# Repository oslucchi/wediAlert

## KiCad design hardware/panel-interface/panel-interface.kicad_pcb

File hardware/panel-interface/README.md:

# wediAlert fire panel interface

Replaces the hand-wired perfboard. Two supervised 12 V loops from the fire panel drive two relays,
whose contacts put 3.3 V on GPIO19 and GPIO26. It also carries the 12 V to 5 V module.
Open `panel-interface.kicad_pro` in KiCad 10.

| Condition | Loop | Relay | GPIO reads | wediAlert sees |
|---|---|---|---|---|
| Normal | closed | energized | 1 | normal |
| Alarm, panel power loss, cut cable | open | released | 0 | active |

No software change is needed: the pins and the logic match `GpioHandler`.

## Check before ordering

- **Board: 92 x 30 mm**, plus 7.5 mm of J1/J2 overhanging one long edge, for the box of 110 x 110 x 60 mm
  with the Pi and HAT alongside. Lay a paper cut-out in the box to check it clears the corner posts, and
  that the plugs and the panel cable have room to bend beyond the overhang.
- **Module: measured** at 52 x 23 mm with pads on a 50 x 21 mm rectangle (`MOD_*` in `gen_sch.py`). The
  board's 1.3 mm pad holes are an assumption: check them against the wire or pin you use.
- **Green plug: confirmed** 5.08 mm pitch.

## Parts

| Ref | Value | Notes |
|---|---|---|
| K1, K2 | FP2 D3009 | Reuse the existing relays. 5 V coil, 178 ohm, polarized |
| R1, R2 | 270 ohm, 0.6 W | Coil series resistor, about 0.2 W dissipated |
| D1, D2 | 1N4148 | Coil flyback. Band to the coil + side, as on the silk |
| F1, F2 | Bourns MF-R010 | Resettable, 100 mA hold, 5.08 mm pitch |
| D3, D4 | LED 3 mm, any color | Panel loop. 4 mA from 12 V |
| R3, R4 | 2.2 k | For D3, D4 |
| D5, D6 | LED 3 mm **red, orange or yellow** | Relay state. Blue or white will not light from 3.3 V |
| R5, R6 | 470 ohm | For D5, D6, about 3 mA |
| R7, R8 | 1 k | GPIO series protection |
| R9, R10 | 10 k | Pull-down. Overrides a leftover Pi pull-up |
| U1 | XL4015 module | Reuse the existing one |
| J1 | 4-way 5.08 mm MSTBA-style header | Mates with your existing green plug (5.08 mm confirmed) |
| J2 | 2-way 5.08 mm MSTBA-style header | 12 V in, with its plug |
| J3 | Solder pads | 5 V wires, 1 mm2 |
| J4 | 1x4 2.54 mm pin header | Dupont wires to the HAT |

The LED footprints can hold the LED directly, or take wires to LEDs on the box wall as today.

## Connections

| Connector | Pin | Signal | Goes to |
|---|---|---|---|
| J1 | 1 / 2 | Line 1 out / return | Panel fault loop |
| J1 | 3 / 4 | Line 2 out / return | Panel alarm loop |
| J2 | 1 / 2 | +12 V / GND | Supply, at least 2 A |
| J3 | 1 / 2 | +5 V / GND | HAT pin 2 / pin 6 |
| J4 | 1 | 3V3 | Pi pin 17 (**new wire**) |
| J4 | 2 | GPIO19 | Pi pin 35 |
| J4 | 3 | GPIO26 | Pi pin 37 |
| J4 | 4 | GND | Pi pin 39 |

Connector labels are on the bottom silkscreen, where they stay readable once parts are fitted.

| LED | Lit when |
|---|---|
| D3 / D5 | Line 1 loop closed / line 1 relay closed |
| D4 / D6 | Line 2 loop closed / line 2 relay closed |

The panel LED goes off for an alarm and for an unplugged cable alike, since both open the loop.

## Bring-up

Keep `wedialert` disabled until the last step.

1. **Before soldering each relay**, with a meter: 178 ohm or so between pins 1 and 10, and continuity
   between 8 and 9. Apply 5 V, + on pin 1 and - on pin 10: it should click, with continuity between
   8 and 7. The datasheet is a 2012 TE edition and these relays are older Alcatel parts, so this
   confirms the pinout before it matters.
2. **Module alone, Pi disconnected:** apply 12 V and set the trimmer to 5.1 V at J3.
3. **Connect J4 and J3 to the Pi.** Power up with nothing on J1. Both inputs must read 0, even after
   forcing a pull-up, because R9/R10 win:
   ```bash
   gpio -g mode 19 up; gpio -g mode 26 up; gpio -g read 19; gpio -g read 26
   ```
4. **Link J1 pins 1-2.** D3 and D5 light, the relay clicks, GPIO19 reads 1. Then the same with
   pins 3-4, for D4, D6 and GPIO26.
5. **Put back the pull-down**, as the service does, and measure 4.5 to 5 V across each coil:
   ```bash
   gpio -g mode 19 down; gpio -g mode 26 down
   ```
6. **On the panel**, check both inputs read 1, then enable the service. Warn the SMS contacts first.
   ```bash
   sudo systemctl enable --now wedialert
   ```

## Rebuilding

`generator/build.sh` regenerates everything from the scripts and runs ERC and DRC. It overwrites the
schematic and board, so hand edits made in KiCad are lost: once you start editing there, stop using it.

After moving a part on the board, run with `ROUTE_SEARCH=1` to find a new routing order (about 30 s per
attempt). The tracks were routed by a script: valid, but less tidy than hand routing.

`out/` holds the schematic PDF, BOM, Gerbers and drill files, and the ERC and DRC reports.

The DRC reports 2 accepted silkscreen warnings: the J1 and J2 outlines overhang the edge by design.

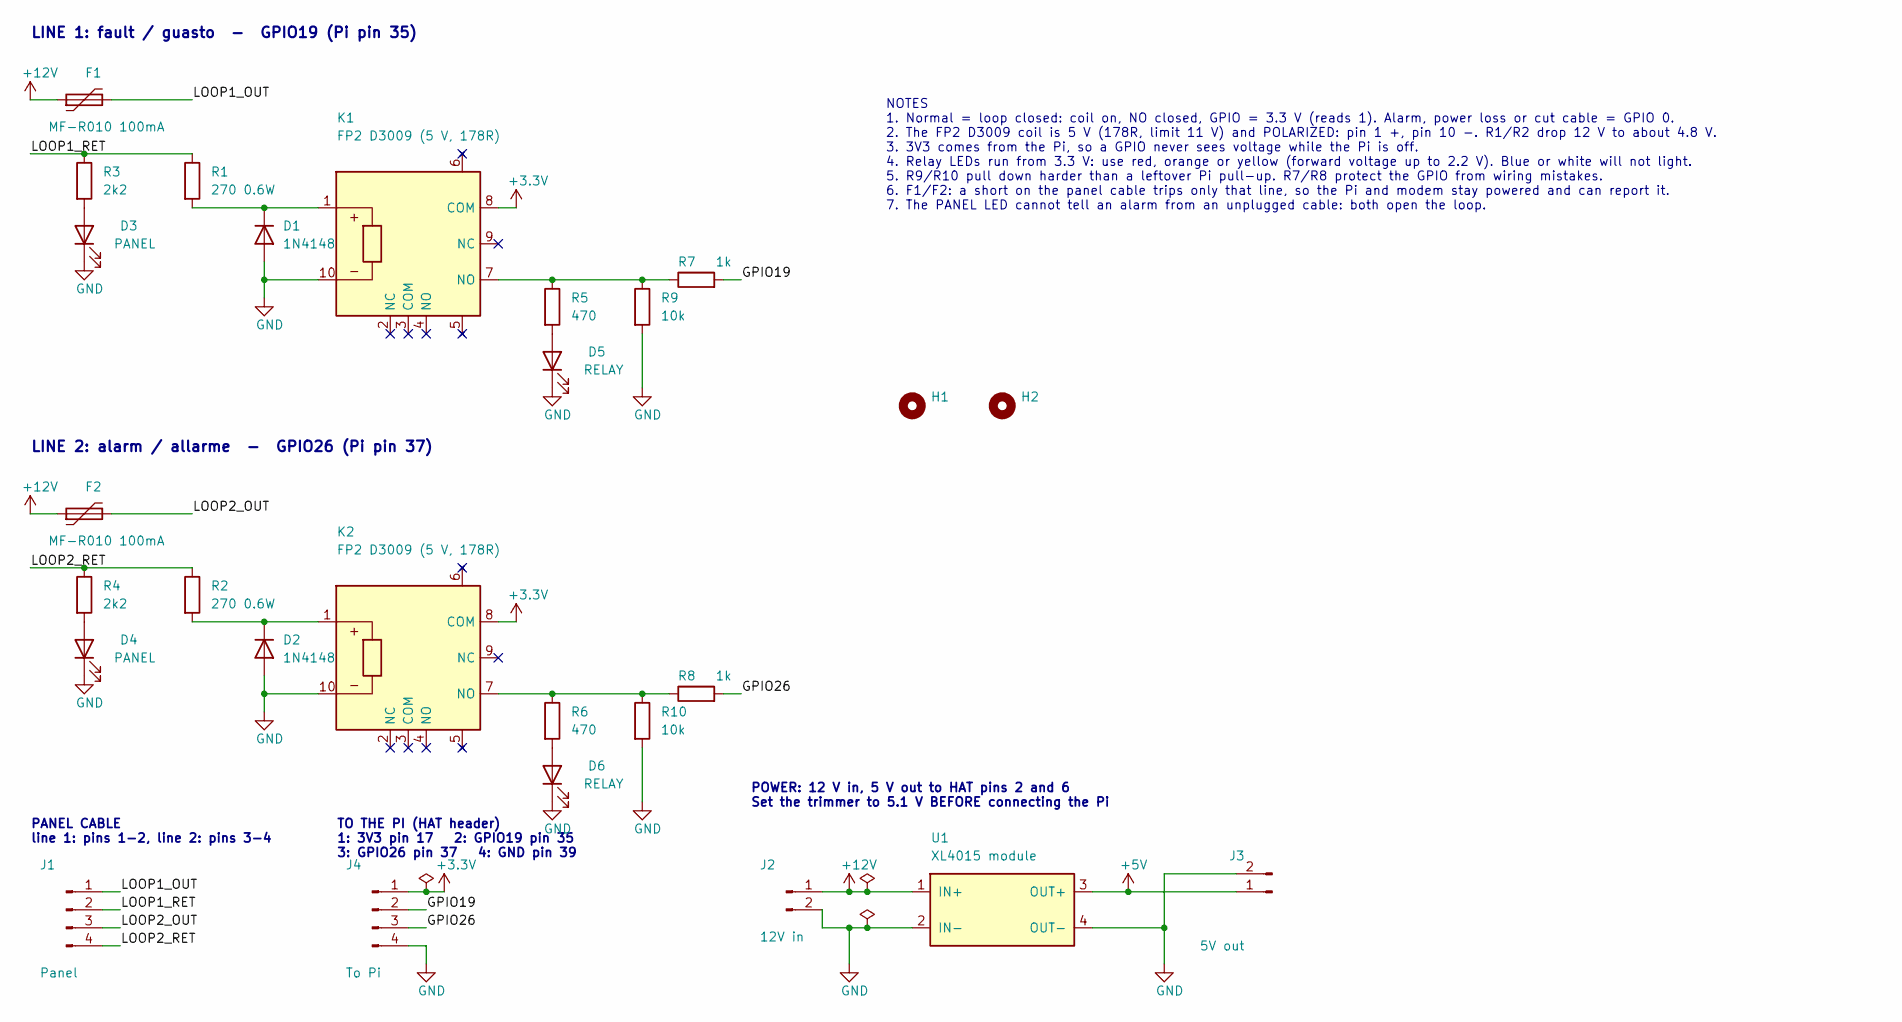
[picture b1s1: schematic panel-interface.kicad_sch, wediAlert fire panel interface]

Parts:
D1, D2: 1N4148; D_DO-35_SOD27_P2.54mm_Vertical_AnodeUp
D3, D4: PANEL; LED_D3.0mm
D5, D6: RELAY; LED_D3.0mm
F1, F2: MF-R010 100mA; Polyfuse_Radial_P5.08mm
H1, H2: M3; Hole_M3
J1: Panel; PhoenixContact_MSTBA_2,5_4-G-5,08_1x04_P5.08mm_Horizontal
J2: 12V in; PhoenixContact_MSTBA_2,5_2-G-5,08_1x02_P5.08mm_Horizontal
J3: 5V out; SolderWire_Pads_1x02_P6mm
J4: To Pi; PinHeader_1x04_P2.54mm_Vertical
K1, K2: FP2 D3009 (5 V, 178R); Relay_DPDT_Axicom_FP2
R1, R2: 270 0.6W; R_Axial_DIN0207_L6.3mm_D2.5mm_P7.62mm_Horizontal
R3, R4: 2k2; R_Axial_DIN0207_L6.3mm_D2.5mm_P2.54mm_Vertical
R5, R6: 470; R_Axial_DIN0207_L6.3mm_D2.5mm_P2.54mm_Vertical
R7, R8: 1k; R_Axial_DIN0207_L6.3mm_D2.5mm_P2.54mm_Vertical
R9, R10: 10k; R_Axial_DIN0207_L6.3mm_D2.5mm_P2.54mm_Vertical
U1: XL4015 module; Buck_Module_XL4015_52x23mm

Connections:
+3.3V: J4.1, K1.8 (COM), K2.8 (COM)
+5V: J3.1, U1.3 (OUT+)
+12V: F1.1, F2.1, J2.1, U1.1 (IN+)
/GPIO19: J4.2, R7.2
/GPIO26: J4.3, R8.2
/LOOP1_OUT: F1.2, J1.1
/LOOP1_RET: J1.2, R1.1, R3.1
/LOOP2_OUT: F2.2, J1.3
/LOOP2_RET: J1.4, R2.1, R4.1
GND: D1.2 (A), D2.2 (A), D3.1 (K), D4.1 (K), D5.1 (K), D6.1 (K), J2.2, J3.2, J4.4, K1.10, K2.10, R9.2, R10.2, U1.2 (IN-), U1.4 (OUT-)
unnamed: D1.1 (K), K1.1, R1.2
unnamed: D2.1 (K), K2.1, R2.2
unnamed: D3.2 (A), R3.2
unnamed: D4.2 (A), R4.2
unnamed: D5.2 (A), R5.2
unnamed: D6.2 (A), R6.2
unnamed: K1.7 (NO), R5.1, R7.1, R9.1
unnamed: K2.7 (NO), R6.1, R8.1, R10.1

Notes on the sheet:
LINE 1: fault / guasto - GPIO19 (Pi pin 35)
LINE 2: alarm / allarme - GPIO26 (Pi pin 37)
PANEL CABLE line 1: pins 1-2, line 2: pins 3-4
TO THE PI (HAT header) 1: 3V3 pin 17 2: GPIO19 pin 35 3: GPIO26 pin 37 4: GND pin 39
POWER: 12 V in, 5 V out to HAT pins 2 and 6 Set the trimmer to 5.1 V BEFORE connecting the Pi
NOTES 1. Normal = loop closed: coil on, NO closed, GPIO = 3.3 V (reads 1). Alarm, power loss or cut cable = GPIO 0. 2. The FP2 D3009 coil is 5 V (178R, limit 11 V) and POLARIZED: pin 1 +, pin 10 -. R1/R2 drop 12 V to about 4.8 V. 3. 3V3 comes from the Pi, so a GPIO never sees voltage while the Pi i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

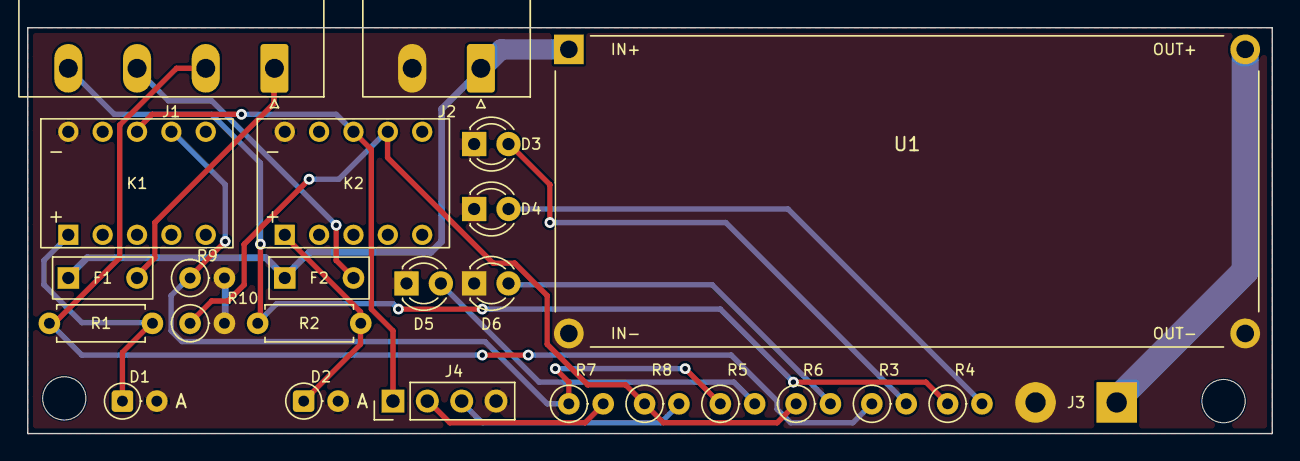
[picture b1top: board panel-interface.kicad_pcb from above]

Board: 2 copper layers, 92.0 x 30.0 mm, 27 parts (0 on the bottom side), 18 nets.

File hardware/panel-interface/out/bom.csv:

"Reference","Value","Footprint","QUANTITY"
"D1,D2","1N4148","Diode_THT:D_DO-35_SOD27_P2.54mm_Vertical_AnodeUp","2"
"D3,D4","PANEL","LED_THT:LED_D3.0mm","2"
"D5,D6","RELAY","LED_THT:LED_D3.0mm","2"
"F1,F2","MF-R010 100mA","panel_interface:Polyfuse_Radial_P5.08mm","2"
"J1","Panel","Connector_Phoenix_MSTB:PhoenixContact_MSTBA_2,5_4-G-5,08_1x04_P5.08mm_Horizontal","1"
"J2","12V in","Connector_Phoenix_MSTB:PhoenixContact_MSTBA_2,5_2-G-5,08_1x02_P5.08mm_Horizontal","1"
"J3","5V out","panel_interface:SolderWire_Pads_1x02_P6mm","1"
"J4","To Pi","Connector_PinHeader_2.54mm:PinHeader_1x04_P2.54mm_Vertical","1"
"K1,K2","FP2 D3009 (5 V, 178R)","panel_interface:Relay_DPDT_Axicom_FP2","2"
"R1,R2","270 0.6W","Resistor_THT:R_Axial_DIN0207_L6.3mm_D2.5mm_P7.62mm_Horizontal","2"
"R3,R4","2k2","Resistor_THT:R_Axial_DIN0207_L6.3mm_D2.5mm_P2.54mm_Vertical","2"
"R5,R6","470","Resistor_THT:R_Axial_DIN0207_L6.3mm_D2.5mm_P2.54mm_Vertical","2"
"R7,R8","1k","Resistor_THT:R_Axial_DIN0207_L6.3mm_D2.5mm_P2.54mm_Vertical","2"
"R9,R10","10k","Resistor_THT:R_Axial_DIN0207_L6.3mm_D2.5mm_P2.54mm_Vertical","2"
"U1","XL4015 module","panel_interface:Buck_Module_XL4015_52x23mm","1"

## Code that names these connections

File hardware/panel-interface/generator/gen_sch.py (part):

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    y = 142.24
    s.text("PANEL CABLE\nline 1: pins 1-2, line 2: pins 3-4", 27.94, y - 10.16, 1.27, True)
    s.place("J1", "Connector:Conn_01x04_Pin", "Panel", 33.02, y + 2.54, 0, FP_MSTB % (4, 4), ref_off=(-3.81, -6.35), val_off=(-3.81, 8.89))
    for pin, net in (("1", "LOOP1_OUT"), ("2", "LOOP1_RET"), ("3", "LOOP2_OUT"), ("4", "LOOP2_RET")):
        q = s.p("J1", pin)
        s.wire(q, (q[0] + 2.54, q[1]))
        s.label(net, (q[0] + 2.54, q[1]))

    # Pi connector
    x = 76.2
    s.text("TO THE PI (HAT header)\n1: 3V3 pin 17   2: GPIO19 pin 35\n3: GPIO26 pin 37   4: GND pin 39", x - 5.08, y - 10.16, 1.27, True)
    s.place("J4", "Connector:Conn_01x04_Pin", "To Pi", x, y + 2.54, 0, FP_HDR, ref_off=(-3.81, -6.35), val_off=(-3.81, 8.89))
    q = s.p("J4", "1")
    s.wire(q, (q[0] + 5.08, q[1]))
    s.power("+3.3V", (q[0] + 5.08, q[1]))
    s.flag((q[0] + 2.54, q[1]))
    s.junction((q[0] + 2.54, q[1]))
    for pin, net in (("2", "GPIO19"), ("3", "GPIO26")):
        q = s.p("J4", pin)
        s.wire(q, (q[0] + 2.54, q[1]))
        s.label(net, (q[0] + 2.54, q[1]))
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        libsyms.append(t.replace('(symbol "%s"' % lib_id.split(":")[1], '(symbol "%s"' % lib_id, 1))
    out = (
        f'(kicad_sch\n\t(version 20250114)\n\t(generator "eeschema")\n\t(generator_version "9.0")\n\t(uuid "{uid("root")}")\n\t(paper "A4")\n'
        '\t(title_block (title "wediAlert fire panel interface") (rev "1") (company "wedi") (comment 1 "2 supervised 12 V loops > relays > GPIO19 / GPIO26, plus 12 V to 5 V supply"))\n'
        "\t(lib_symbols\n" + "\n".join(libsyms) + "\n\t)\n" + "\n".join(s.body) + "\n"
        f'\t(sheet_instances (path "/" (page "1")))\n\t(embedded_fonts no)\n)\n'
    )
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
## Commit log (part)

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2023-09-30 project init
2023-10-02 added gpio handler
2023-10-02 cosmetics
2023-10-02 compiled
2023-10-02 added WiringPi lib
2023-10-02 added WiringPi library
2023-10-03 tested response on pin change status. MSG sent
2023-10-04 still issue on getting expected from multi message return
2023-10-04 Completed test sending messages to list from propoerties file
2023-10-09 version ready to test on Oct 9th
2023-10-16 released to production
